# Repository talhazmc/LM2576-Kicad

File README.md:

# LM2576 Adjustable Buck Converter PCB Design

This repository contains my KiCad PCB design project based on the LM2576 adjustable step-down switching regulator.

The project was designed as a DC-DC buck converter module that converts a higher DC input voltage to a lower adjustable DC output voltage. The PCB includes input/output terminal blocks, power components, feedback components, and a compact board layout.

---

## Project Overview

The main purpose of this project was to design a practical power electronics PCB using KiCad.

The circuit is based on the LM2576ADJ regulator. It uses an inductor, diode, input/output capacitors, and a feedback network to generate an adjustable regulated output voltage.

This type of circuit is commonly used in embedded systems and electronic projects where a stable lower DC voltage is required from a higher DC supply.

---

## 3D PCB View

The 3D view shows the physical placement of the main components, including the LM2576 regulator, inductor, capacitors, potentiometer, diode, and input/output connectors.

---

## PCB Layout

The PCB layout was created in KiCad.
The board includes wide power traces and separated input/output sections for better current handling and readability.

---

## Main Components

* LM2576ADJ switching regulator
* Inductor
* Schottky diode
* Input capacitor
* Output capacitor
* Feedback resistor
* Adjustable potentiometer
* Input terminal block
* Output terminal block
* GND and VCC connections

---

## Working Principle

The LM2576 works as a step-down switching regulator.

The input voltage is applied to the input terminal. The LM2576 switches the current through the inductor, while the diode and capacitors help smooth and regulate the output voltage.

The feedback network, including the potentiometer, is used to adjust the output voltage level. By changing the feedback ratio, the regulator changes its duty cycle and maintains the desired output voltage.

The output terminal provides the regulated lower DC voltage for external circuits.

---

## PCB Design Notes

* Input and output sections were clearly labeled as **GIRIS** and **CIKIS**
* Terminal blocks were used for easy external connection
* Power traces were designed wider than signal traces
* The feedback and adjustment components were placed close to the regulator
* The board was checked using KiCad 3D Viewer

---

## What I Learned

Through this project, I gained practical experience in:

* Designing a switching regulator PCB
* Using KiCad for PCB layout and 3D visualization
* Understanding LM2576 buck converter operation
* Placing power components on a PCB
* Routing high-current paths
* Designing input/output terminal connections
* Creating a compact power supply module

---

## Tools and Technologies

* KiCad
* LM2576ADJ
* DC-DC buck converter
* PCB design
* Power electronics
* Switching regulator
* 3D PCB visualization

---

## Author

**Talha Üzümcü**
Electrical and Electronics Engineer
GitHub: [talhazmc](https://github.com/talhazmc)

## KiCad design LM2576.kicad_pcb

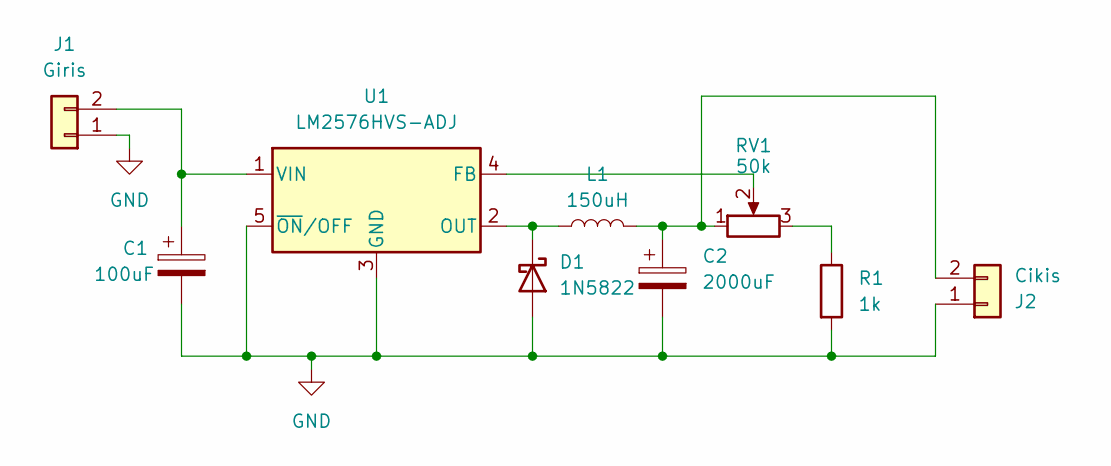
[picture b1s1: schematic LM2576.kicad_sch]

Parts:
C1: 100uF; CP_Elec_6.3x7.7
C2: 2000uF; CP_Elec_16x17.5
D1: 1N5822; D_SMA_Handsoldering
J1: Giris; PhoenixContact_MC_1,5_2-G-3.5_1x02_P3.50mm_Horizontal
J2: Cikis; PhoenixContact_MC_1,5_2-G-3.5_1x02_P3.50mm_Horizontal
L1: 150uH; L_Wuerth_HCI-1030
R1: 1k; R_1206_3216Metric
RV1: 50k; Potentiometer_Bourns_3296W_Vertical
U1: LM2576HVS-ADJ; TO-263-5_TabPin3

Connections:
GND: C1.2, C2.2, D1.2 (A), J1.1, J2.1, R1.2, U1.3 (GND), U1.5 (~ON/OFF)
unnamed: D1.1 (K), L1.1, U1.2 (OUT)
unnamed: C1.1, J1.2, U1.1 (VIN)
unnamed: C2.1, J2.2, L1.2, RV1.1
unnamed: R1.1, RV1.3
unnamed: RV1.2, U1.4 (FB)

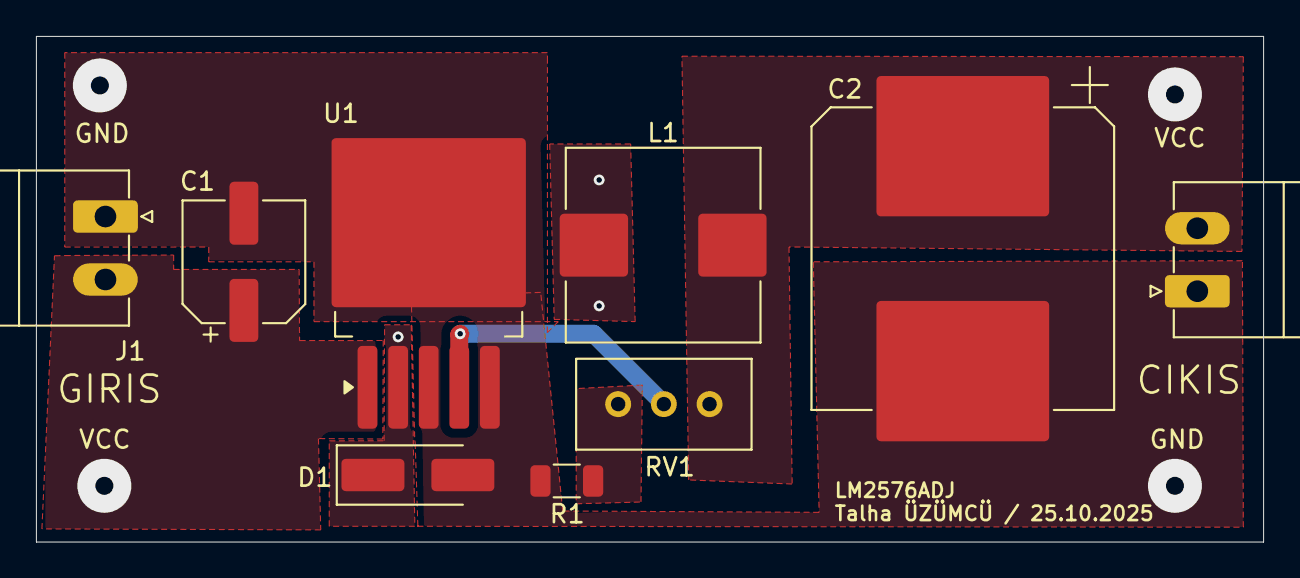
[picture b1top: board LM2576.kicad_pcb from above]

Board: 2 copper layers, 68.2 x 28.1 mm, 9 parts (0 on the bottom side), 6 nets.

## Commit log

2026-06-24 images
2026-06-24 Add README for LM2576 Adjustable Buck Converter project
    This README provides an overview of the LM2576 adjustable buck converter PCB design project, including its components, working principle, and design notes.
